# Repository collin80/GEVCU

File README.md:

GEVCU
=====

Generalized Electric Vehicle Control Unit

A project to create a fairly Arduino compatible ECU firmware
to interface with various electric vehicle hardware over canbus
(and possibly other comm channels)

The project builds in the Arduino IDE. So, use it to compile, send the firmware to the Arduino, and monitor serial.
It is suggested though to use the Eclipse based Arduino Plugin by Sloeber which provides far superior capabilities.

The master branch of this project provides a stable code base. The main development happens on the development branch or feature branches if necessary.
If the code on development branch is stable (end tested in practice by the developers), it is merged into the master branch.

You will need the following to have any hope of compiling and running the firmware:
- A GEVCU board. (Versions from 2 upward are supported)
- THe latest Arduino IDE (or preferably Eclipse with ArduinoPlugin by Sloeber)
- due_can library by Collin Kidder
- due_wire library by Collin Kidder
- DueTimer library by Collin Kidder
- PID library by Brett Beauregard

All libraries belong in %USERPROFILE%\Documents\Arduino\libraries (Windows) or ~/Arduino/libraries (Linux/Mac).
You will need to remove -master or any other postfixes. Your library folders should be named as above.

If you use a GEVCU 2.x, please change the pin assignments for CFG_EEPROM_WRITE_PROTECT and CFG_WIFI_RESET in config.h according to comment.      

This software is MIT licensed:

Copyright (c) 2014-2020 Collin Kidder, Michael Neuweiler, Charles Galpin, Jack Rickard

Permission is hereby granted, free of charge, to any person obtaining
a copy of this software and associated documentation files (the
"Software"), to deal in the Software without restriction, including
without limitation the rights to use, copy, modify, merge, publish,
distribute, sublicense, and/or sell copies of the Software, and to
permit persons to whom the Software is furnished to do so, subject to
the following conditions:

The above copyright notice and this permission notice shall be included
in all copies or substantial portions of the Software.

THE SOFTWARE IS PROVIDED "AS IS", WITHOUT WARRANTY OF ANY KIND,
EXPRESS OR IMPLIED, INCLUDING BUT NOT LIMITED TO THE WARRANTIES OF
MERCHANTABILITY, FITNESS FOR A PARTICULAR PURPOSE AND NONINFRINGEMENT.
IN NO EVENT SHALL THE AUTHORS OR COPYRIGHT HOLDERS BE LIABLE FOR ANY
CLAIM, DAMAGES OR OTHER LIABILITY, WHETHER IN AN ACTION OF CONTRACT,
TORT OR OTHERWISE, ARISING FROM, OUT OF OR IN CONNECTION WITH THE
SOFTWARE OR THE USE OR OTHER DEALINGS IN THE SOFTWARE.

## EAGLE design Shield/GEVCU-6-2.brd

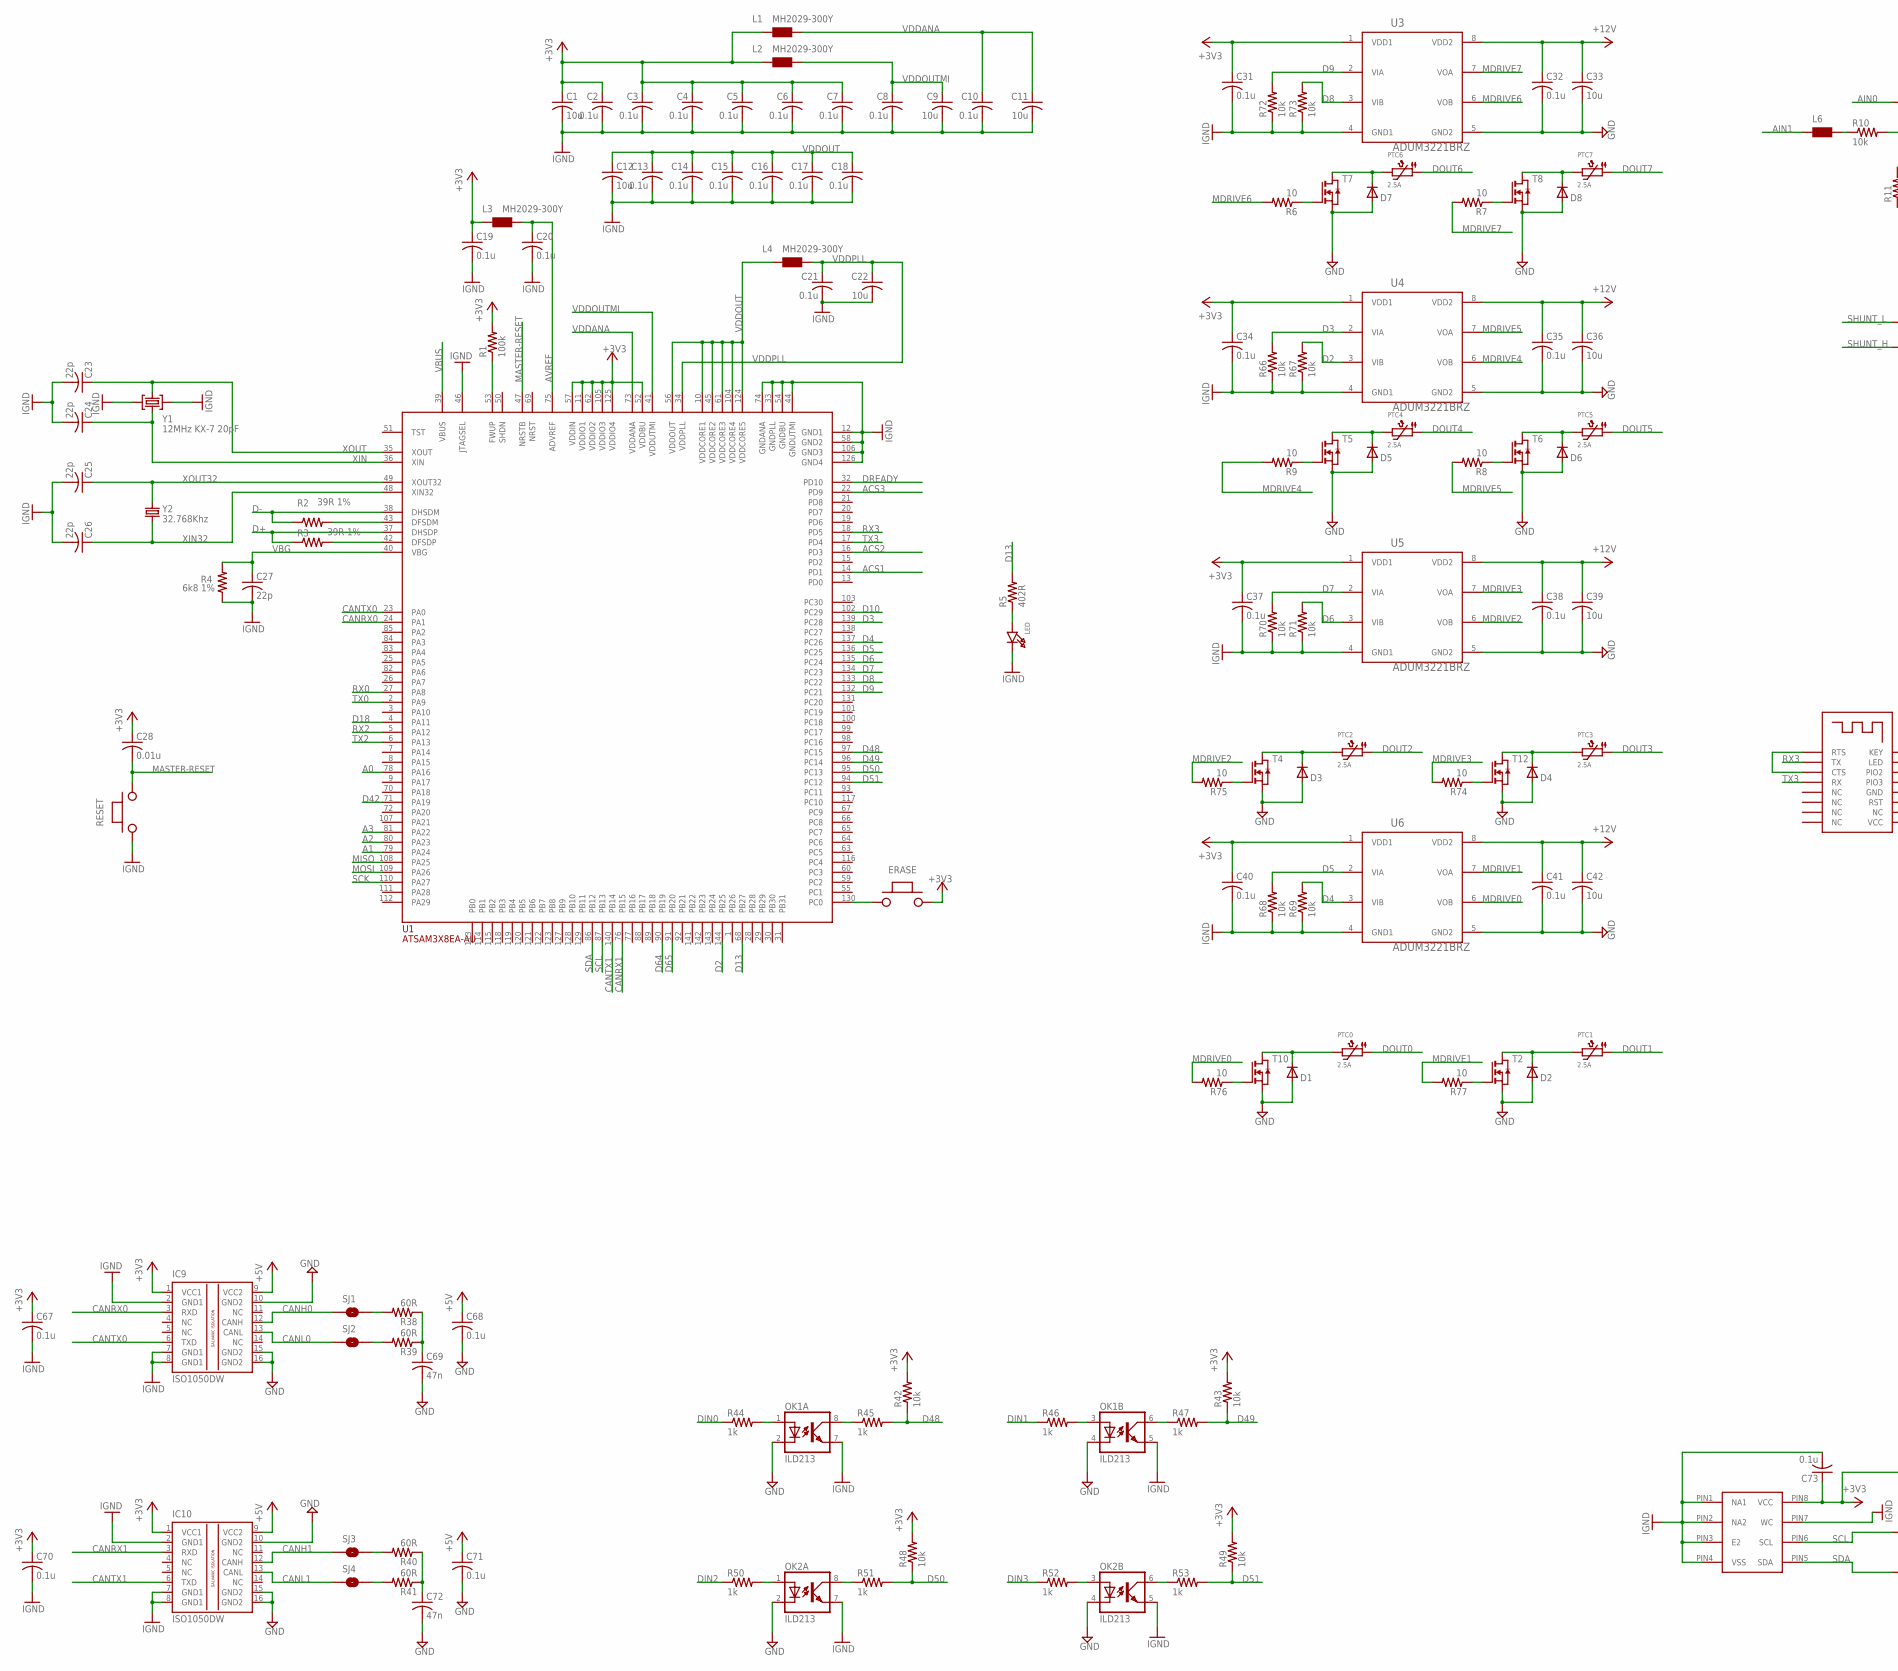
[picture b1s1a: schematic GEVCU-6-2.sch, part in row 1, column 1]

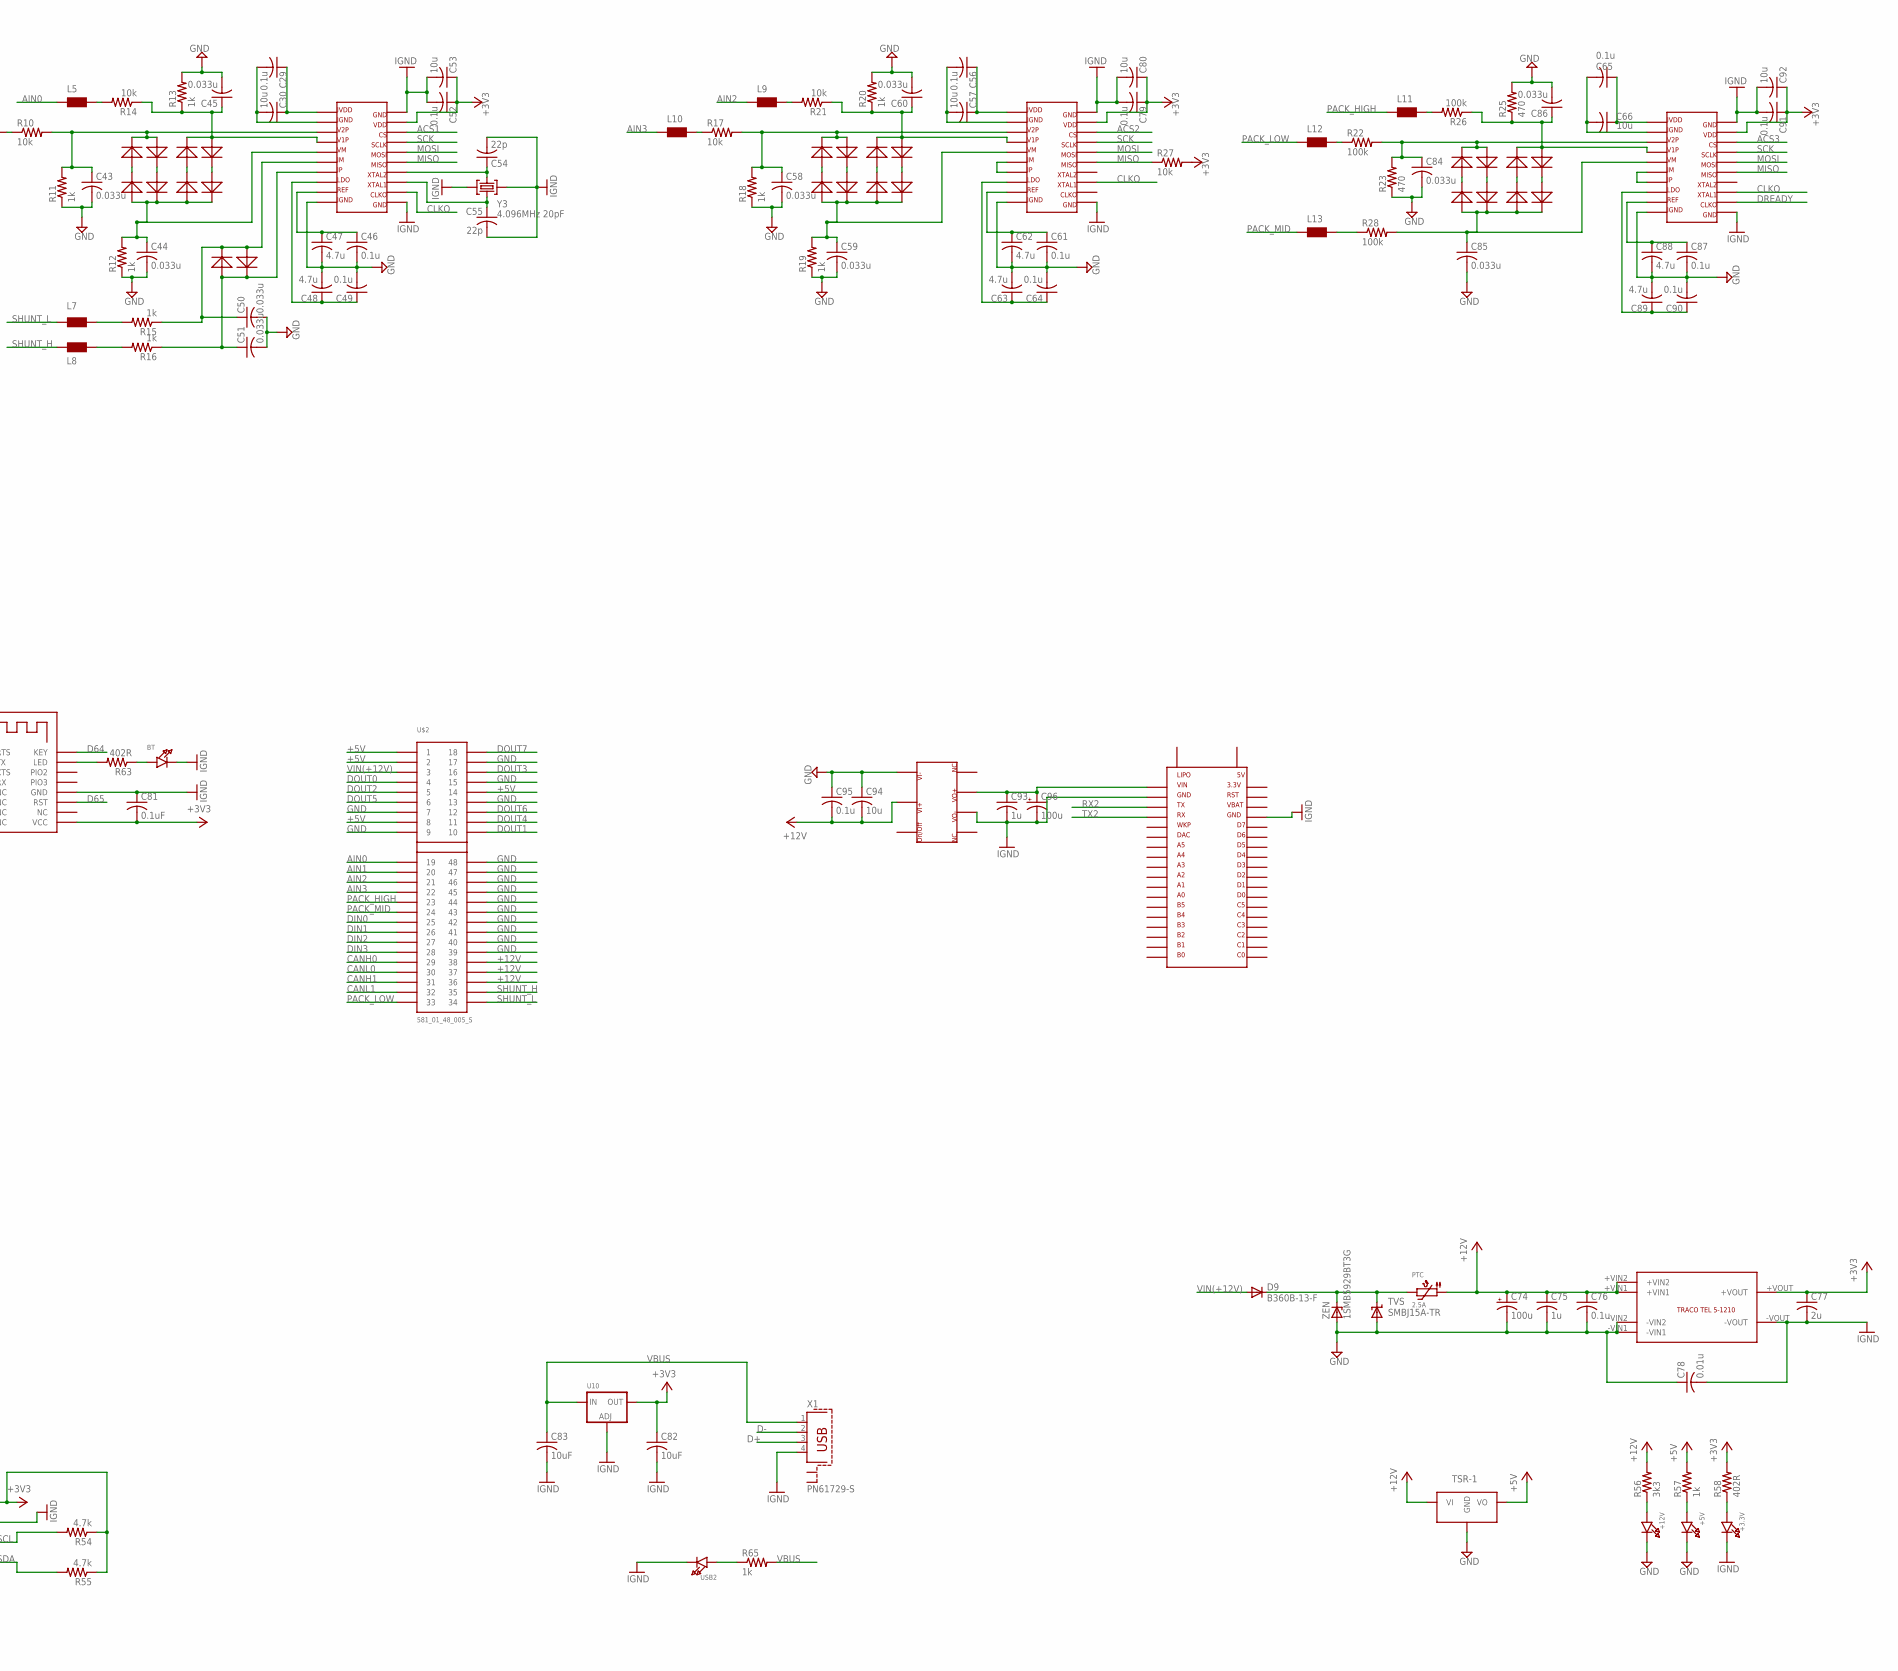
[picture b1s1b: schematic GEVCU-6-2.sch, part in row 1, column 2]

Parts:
+3.3V, +5V, +12V: LED0805; CHIPLED_0805
BT: LED0805; CHIPLED_0805
C1, C9, C11, C12, C22, C30, C33, C36, C39, C42, C53, C57, C66, C80, C92, C94: 10u; C0805
C2, C3, C4, C5, C6, C7, C8, C10, C13, C14, C15, C16, C17, C18, C19, C20, C21, C29, C31, C32, C34, C35, C37, C38, C40, C41, C46, C49, C52, C56, C61, C64, C65, C67, C68, C70, C71, C73, C76, C79, C87, C90, C91, C95: 0.1u; C0805
C23, C24, C54, C55: 22p; C1206
C25, C26, C27: 22p; C0805
C28: 0.01u; C0805
C43, C44, C45, C50, C51, C58, C59, C60, C84, C85, C86: 0.033u; C0805
C47, C48, C62, C63, C88, C89: 4.7u; C0805
C69, C72: 47n; C0805
C74, C96: 100u; E2,5-6
C75, C93: 1u; C0805
C77: 2u; C0805
C78: 0.01u; C1812
C81: 0.1uF; C0805
C82, C83: 10uF; C0805
D1, D2, D3, D4, D5, D6, D7, D8: MBR0520LT; SOD123
D9: B360B-13-F; SMB
D10, D11, D12, D13, D14, D15, D16, D17, D18, D19, D20, D21, D22, D23, D24, D25, D26, D27, D28, D29, D30, D31, D32, D33, D34, D35: SIGDIODE; R0603
ERASE: PUCHBUTTON
IC9, IC10: ISO1050DW; DUB-R-PDSO-G8
L1, L2, L3, L4, L5, L6, L7, L8, L9, L10, L11, L12, L13: MH2029-300Y; 0805
LED: LED0805; CHIPLED_0805
OK1, OK2: ILD213; SOIC08
PTC, PTC0, PTC1, PTC2, PTC3, PTC4, PTC5, PTC6, PTC7: 2.5A; PTC1812
R1, R22, R26, R28: 100k; R0805
R2, R3: 39R 1%; R0805
R4: 6k8 1%; R0805
R5, R58, R63: 402R; R0805
R6, R7, R8, R9, R74, R75, R76, R77: 10; R0805
R10, R14, R17, R21, R27, R42, R43, R48, R49, R66, R67, R68, R69, R70, R71, R72, R73: 10k; R0805
R11, R12, R13, R15, R16, R18, R19, R20, R44, R45, R46, R47, R50, R51, R52, R53, R57, R65: 1k; R0805
R23, R25: 470; R0805
R38, R39, R40, R41: 60R; R0805
R54, R55: 4.7k; R0805
R56: 3k3; R0805
RESET: PUCHBUTTON
SJ1, SJ2, SJ3, SJ4: SOLDERJUMPERNO; SJ_2S-NO
T2, T4, T5, T6, T7, T8, T10, T12: NMOSSOT223; SOT223
TVS: SMBJ15A-TR; SMBJ
U1: ATSAM3X8EA-AU; LQFP144
U3, U4, U5, U6: ADUM3221BRZ; SOIC127P600X175-8N
U7: CK_CUSTOM_M24M02-DRMN6TP; CK_CUSTOM_SOIC8
U8: TRACO
U9: TSR-1
U10: LM1117SOT223-WAVE; SOT223-W
U11, U12, U24: ADE7913; SOIC20
U13: HM-13
U15: ELECTRON
U$1: CINCON5V
U$2: 581_01_48_005_S
USB2: LED0805; CHIPLED_0805
X1: PN61729-S
Y1: 12MHz KX-7 20pF; CRYSTAL-3.2-2.5
Y2: 32.768Khz; ARDUINO_WIFI_SHIELD_V018_TG_RESONATOR_EPSON_FC_145
Y3: 4.096MHz 20pF; CRYSTAL-3.2-2.5
ZEN: 1SMB5929BT3G; SMB

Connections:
+3V3: C1.1, C2.1, C3.1, C4.1, C5.1, C6.1, C7.1, C19.1, C28.1, C31.1, C34.1, C37.1, C40.1, C52.1, C53.1, C67.1, C70.1, C73.1, C77.1, C79.1, C80.1, C81.2, C82.1, C91.1, C92.1, ERASE.P$2, IC9.1 (VCC1), IC10.1 (VCC1), L1.1, L2.1, L3.1, R1.2, R27.2, R42.2, R43.2, R48.2, R49.2, R54.1, R55.1, R58.2, U1.11 (VDDIO1), U1.52 (VDDBU), U1.57 (VDDIN), U1.62 (VDDIO2), U1.105 (VDDIO3), U1.125 (VDDIO4), U3.1 (VDD1), U4.1 (VDD1), U5.1 (VDD1), U6.1 (VDD1), U7.PIN8 (VCC), U8.+VOUT, U10.2 (OUT), U11.19, U12.19, U13.P$9 (VCC), U24.19
+5V: C68.1, C71.1, IC9.9 (VCC2), IC10.9 (VCC2), R57.2, U9.P$3 (VO), U$2.P$1 (1), U$2.P$2 (2), U$2.P$8 (8), U$2.P$14 (14)
+12V: C32.1, C33.1, C35.1, C36.1, C38.1, C39.1, C41.1, C42.1, C74.+, C75.1, C76.1, C94.2, C95.2, PTC.P$1 (1), R56.2, U3.8 (VDD2), U4.8 (VDD2), U5.8 (VDD2), U6.8 (VDD2), U8.+VIN1, U8.+VIN2, U9.P$1 (VI), U$1.P$2, U$2.P$36 (36), U$2.P$37 (37), U$2.P$38 (38)
A0: U1.78 (PA16)
A1: U1.79 (PA24)
A2: U1.80 (PA23)
A3: U1.81 (PA22)
ACS1: U1.14 (PD1), U11.18
ACS2: U1.16 (PD3), U12.18
ACS3: U1.22 (PD9), U24.18
AIN0: L5.1, U$2.P$19 (19)
AIN1: L6.1, U$2.P$20 (20)
AIN2: L9.1, U$2.P$21 (21)
AIN3: L10.1, U$2.P$22 (22)
AVREF: C20.1, L3.2, U1.75 (ADVREF)
CANH0: IC9.12 (CANH), SJ1.1, U$2.P$29 (29)
CANH1: IC10.12 (CANH), SJ3.1, U$2.P$31 (31)
CANL0: IC9.13 (CANL), SJ2.1, U$2.P$30 (30)
CANL1: IC10.13 (CANL), SJ4.1, U$2.P$32 (32)
CANRX0: IC9.3 (RXD), U1.24 (PA1)
CANRX1: IC10.3 (RXD), U1.76 (PB15)
CANTX0: IC9.6 (TXD), U1.23 (PA0)
CANTX1: IC10.6 (TXD), U1.140 (PB14)
CLKO: U11.12, U12.13, U24.13
D2: R67.2, U1.144 (PB25), U4.3 (VIB)
D3: R66.2, U1.139 (PC28), U4.2 (VIA)
D4: R69.2, U1.137 (PC26), U6.3 (VIB)
D5: R68.2, U1.136 (PC25), U6.2 (VIA)
D6: R71.2, U1.135 (PC24), U5.3 (VIB)
D7: R70.2, U1.134 (PC23), U5.2 (VIA)
D8: R73.2, U1.133 (PC22), U3.3 (VIB)
D9: R72.2, U1.132 (PC21), U3.2 (VIA)
D10: U1.102 (PC29)
D13: R5.2, U1.68 (PB27)
D18: U1.4 (PA11)
D42: U1.71 (PA19)
D48: R42.1, R45.2, U1.97 (PC15)
D49: R43.1, R47.2, U1.96 (PC14)
D50: R48.1, R51.2, U1.95 (PC13)
D51: R49.1, R53.2, U1.94 (PC12)
D64: U1.90 (PB19), U13.P$16 (KEY)
D65: U1.91 (PB20), U13.P$11 (RST)
D+: R3.1, U1.37 (DHSDP), X1.3
D-: R2.1, U1.38 (DHSDM), X1.2
DIN0: R44.1, U$2.P$25 (25)
DIN1: R46.1, U$2.P$26 (26)
DIN2: R50.1, U$2.P$27 (27)
DIN3: R52.1, U$2.P$28 (28)
DOUT0: PTC0.P$1 (1), U$2.P$4 (4)
DOUT1: PTC1.P$1 (1), U$2.P$10 (10)
DOUT2: PTC2.P$1 (1), U$2.P$5 (5)
DOUT3: PTC3.P$1 (1), U$2.P$16 (16)
DOUT4: PTC4.P$1 (1), U$2.P$11 (11)
DOUT5: PTC5.P$1 (1), U$2.P$6 (6)
DOUT6: PTC6.P$1 (1), U$2.P$12 (12)
DOUT7: PTC7.P$1 (1), U$2.P$18 (18)
DREADY: U1.32 (PD10), U24.12
ERASE_S: ERASE.P$1, U1.130 (PC0)
GND: +5V.C, +12V.C, C32.2, C33.2, C35.2, C36.2, C38.2, C39.2, C41.2, C42.2, C43.2, C44.2, C45.2, C46.2, C47.2, C48.2, C49.2, C50.2, C51.2, C58.2, C59.2, C60.2, C61.2, C62.2, C63.2, C64.2, C68.2, C69.2, C71.2, C72.2, C74.-, C75.2, C76.2, C78.1, C84.2, C85.2, C86.2, C87.2, C88.2, C89.2, C90.2, C94.1, C95.1, D1.A, D2.A, D3.A, D4.A, D5.A, D6.A, D7.A, D8.A, IC9.10 (GND2), IC9.15 (GND2), IC9.16 (GND2), IC10.10 (GND2), IC10.15 (GND2), IC10.16 (GND2), OK1.2 (C), OK1.4 (C), OK2.2 (C), OK2.4 (C), R11.1, R12.1, R13.2, R18.1, R19.1, R20.2, R23.1, R25.2, T2.3 (S), T4.3 (S), T5.3 (S), T6.3 (S), T7.3 (S), T8.3 (S), T10.3 (S), T12.3 (S), TVS.A, U3.5 (GND2), U4.5 (GND2), U5.5 (GND2), U6.5 (GND2), U8.-VIN1, U8.-VIN2, U9.P$2 (GND), U11.10, U12.10, U24.10, U$1.P$1, U$2.P$7 (7), U$2.P$9 (9), U$2.P$13 (13), U$2.P$15 (15), U$2.P$17 (17), U$2.P$39 (39), U$2.P$40 (40), U$2.P$41 (41), U$2.P$42 (42), U$2.P$43 (43), U$2.P$44 (44), U$2.P$45 (45), U$2.P$46 (46), U$2.P$47 (47), U$2.P$48 (48), ZEN.A
IGND: +3.3V.C, BT.C, C1.2, C2.2, C3.2, C4.2, C5.2, C6.2, C7.2, C8.2, C9.2, C10.2, C11.2, C12.2, C13.2, C14.2, C15.2, C16.2, C17.2, C18.2, C19.2, C20.2, C21.2, C22.2, C23.2, C24.2, C25.2, C26.2, C27.2, C31.2, C34.2, C37.2, C40.2, C52.2, C53.2, C54.2, C55.2, C67.2, C70.2, C73.2, C77.2, C78.2, C79.2, C80.2, C81.1, C82.2, C83.2, C91.2, C92.2, C93.2, C96.-, IC9.2 (GND1), IC9.7 (GND1), IC9.8 (GND1), IC10.2 (GND1), IC10.7 (GND1), IC10.8 (GND1), LED.C, OK1.5 (EMIT), OK1.7 (EMIT), OK2.5 (EMIT), OK2.7 (EMIT), R4.1, R66.1, R67.1, R68.1, R69.1, R70.1, R71.1, R72.1, R73.1, RESET.P$1, U1.12 (GND1), U1.33 (GNDPLL), U1.44 (GNDUTMI), U1.46 (JTAGSEL), U1.54 (GNDBU), U1.58 (GND2), U1.74 (GNDANA), U1.106 (GND3), U1.126 (GND4), U3.4 (GND1), U4.4 (GND1), U5.4 (GND1), U6.4 (GND1), U7.PIN1 (NA1), U7.PIN2 (NA2), U7.PIN3 (E2), U7.PIN4 (VSS), U7.PIN7 (WC), U8.-VOUT, U10.1 (ADJ), U11.11, U11.20, U12.11, U12.20, U13.P$12 (GND), U15.P$17, U15.P$33, U24.11, U24.20, U$1.P$6, USB2.C, X1.4, Y1.2 (GND), Y1.4 (GND), Y3.2 (GND), Y3.4 (GND)
MASTER-RESET: C28.2, RESET.P$2, U1.47 (NRSTB)
MDRIVE0: R76.2, U6.6 (VOB)
MDRIVE1: R77.2, U6.7 (VOA)
MDRIVE2: R75.2, U5.6 (VOB)
MDRIVE3: R74.2, U5.7 (VOA)
MDRIVE4: R9.2, U4.6 (VOB)
MDRIVE5: R8.2, U4.7 (VOA)
MDRIVE6: R6.2, U3.6 (VOB)
MDRIVE7: R7.2, U3.7 (VOA)
MISO: R27.1, U1.108 (PA25), U11.15, U12.15, U24.15
MOSI: U1.109 (PA26), U11.16, U12.16, U24.16
unnamed: D12.2, D13.1
unnamed: +3.3V.A, R58.1
unnamed: D9.C, PTC.P$2 (2), TVS.C, ZEN.C
unnamed: +5V.A, R57.1
unnamed: C29.1, C30.1, U11.1
unnamed: LED.A, R5.1
unnamed: U13.P$1 (RTS), U13.P$3 (CTS)
unnamed: D10.2, D11.1
unnamed: C45.1, D14.2, D16.1, R13.1, R14.1, U11.4
unnamed: C29.2, C30.2, U11.2
unnamed: C43.1, D11.2, D12.1, R10.2, R11.2, U11.3
unnamed: L5.2, R14.2
unnamed: C44.1, D10.1, D13.2, D15.1, D17.2, R12.2, U11.5
unnamed: C65.1, C66.1, U24.1
unnamed: C46.1, C47.1, U11.9
unnamed: C48.1, C49.1, U11.8
unnamed: L6.2, R10.1
unnamed: D16.2, D17.1
unnamed: D14.1, D15.2
unnamed: C50.1, D18.2, D19.1, R15.1, U11.6
unnamed: C51.1, D18.1, D19.2, R16.1, U11.7
unnamed: L7.1, R15.2
unnamed: C56.1, C57.1, U12.1
unnamed: C69.1, R38.1, R39.1
unnamed: L8.1, R16.2
unnamed: R38.2, SJ1.2
unnamed: R39.2, SJ2.2
unnamed: R41.2, SJ4.2
unnamed: C72.1, R40.1, R41.1
unnamed: R40.2, SJ3.2
unnamed: OK1.1 (A), R44.2
unnamed: OK1.3 (A), R46.2
unnamed: OK1.8 (COL), R45.1
unnamed: OK1.6 (COL), R47.1
unnamed: C56.2, C57.2, U12.2
unnamed: OK2.6 (COL), R53.1
unnamed: D22.2, D23.1
unnamed: OK2.8 (COL), R51.1
unnamed: C65.2, C66.2, U24.2
unnamed: OK2.1 (A), R50.2
unnamed: C54.1, U11.14, Y3.3 (C2)
unnamed: C55.1, U11.13, Y3.1 (C1)
unnamed: OK2.3 (A), R52.2
unnamed: +12V.A, R56.1
unnamed: D20.1, D21.2
unnamed: BT.A, R63.1
unnamed: R63.2, U13.P$15 (LED)
unnamed: D2.C, PTC1.P$2 (2), T2.2 (D), T2.4 (D)
unnamed: C58.1, D20.2, D22.1, R17.2, R18.2, U12.3
unnamed: D26.2, D27.1
unnamed: D3.C, PTC2.P$2 (2), T4.2 (D), T4.4 (D)
unnamed: D24.1, D25.2
unnamed: R2.2, U1.43 (DFSDM)
unnamed: C59.1, D21.1, D23.2, D25.1, D27.2, R19.2, U12.5
unnamed: C60.1, D24.2, D26.1, R20.1, R21.1, U12.4
unnamed: R3.2, U1.42 (DFSDP)
unnamed: D5.C, PTC4.P$2 (2), T5.2 (D), T5.4 (D)
unnamed: D6.C, PTC5.P$2 (2), T6.2 (D), T6.4 (D)
unnamed: R1.1, U1.53 (FWUP)
unnamed: D7.C, PTC6.P$2 (2), T7.2 (D), T7.4 (D)
unnamed: D8.C, PTC7.P$2 (2), T8.2 (D), T8.4 (D)
unnamed: D4.C, PTC3.P$2 (2), T12.2 (D), T12.4 (D)
unnamed: D1.C, PTC0.P$2 (2), T10.2 (D), T10.4 (D)
unnamed: D30.2, D31.1
unnamed: C61.1, C62.1, U12.9
unnamed: R65.1, USB2.A
unnamed: R6.1, T7.1 (G)
unnamed: R76.1, T10.1 (G)
unnamed: R77.1, T2.1 (G)
unnamed: R74.1, T12.1 (G)
unnamed: R75.1, T4.1 (G)
unnamed: R9.1, T5.1 (G)
unnamed: R8.1, T6.1 (G)
unnamed: R7.1, T8.1 (G)
unnamed: C63.1, C64.1, U12.8
unnamed: L9.2, R21.2
unnamed: L10.2, R17.1
unnamed: U12.6, U12.7
unnamed: D28.1, D29.2
unnamed: C84.1, D28.2, D30.1, R22.2, R23.2, U24.3
unnamed: D34.2, D35.1
unnamed: D32.1, D33.2
unnamed: C85.1, D29.1, D31.2, D33.1, D35.2, R28.2, U24.5
unnamed: C86.1, D32.2, D34.1, R25.1, R26.1, U24.4
unnamed: C87.1, C88.1, U24.9
unnamed: C89.1, C90.1, U24.8
unnamed: L11.2, R26.2
unnamed: L12.2, R22.1
unnamed: U24.6, U24.7
unnamed: C93.1, C96.+, U15.P$18, U$1.P$5
unnamed: L13.2, R28.1
PACK_HIGH: L11.1, U$2.P$23 (23)
PACK_LOW: L12.1, U$2.P$33 (33)
PACK_MID: L13.1, U$2.P$24 (24)
RX0: U1.27 (PA8)
RX2: U1.5 (PA12), U15.P$16
RX3: U1.18 (PD5), U13.P$2 (TX)
SCK: U1.110 (PA27), U11.17, U12.17, U24.17
SCL: R54.2, U1.87 (PB13), U7.PIN6 (SCL)
SDA: R55.2, U1.86 (PB12), U7.PIN5 (SDA)
SHUNT_H: L8.2, U$2.P$35 (35)
SHUNT_L: L7.2, U$2.P$34 (34)
TX0: U1.2 (PA9)
TX2: U1.6 (PA13), U15.P$15
TX3: U1.17 (PD4), U13.P$4 (RX)
VBG: C27.1, R4.2, U1.40 (VBG)
VBUS: C83.1, R65.2, U1.39 (VBUS), U10.3 (IN), X1.1
VDDANA: C10.1, C11.1, L1.2, U1.73 (VDDANA)
VDDOUT: C12.1, C13.1, C14.1, C15.1, C16.1, C17.1, C18.1, L4.1, U1.10 (VDDCORE1), U1.45 (VDDCORE2), U1.56 (VDDOUT), U1.61 (VDDCORE3), U1.104 (VDDCORE4), U1.124 (VDDCORE5)
VDDOUTMI: C8.1, C9.1, L2.2, U1.41 (VDDUTMI)
VDDPLL: C21.1, C22.1, L4.2, U1.34 (VDDPLL)
VIN(+12V): D9.A, U$2.P$3 (3)
XIN: C24.1, U1.36 (XIN), Y1.1 (C1)
XIN32: C26.1, U1.48 (XIN32), Y2.P$2 (2)
XOUT: C23.1, U1.35 (XOUT), Y1.3 (C2)
XOUT32: C25.1, U1.49 (XOUT32), Y2.P$1 (1)

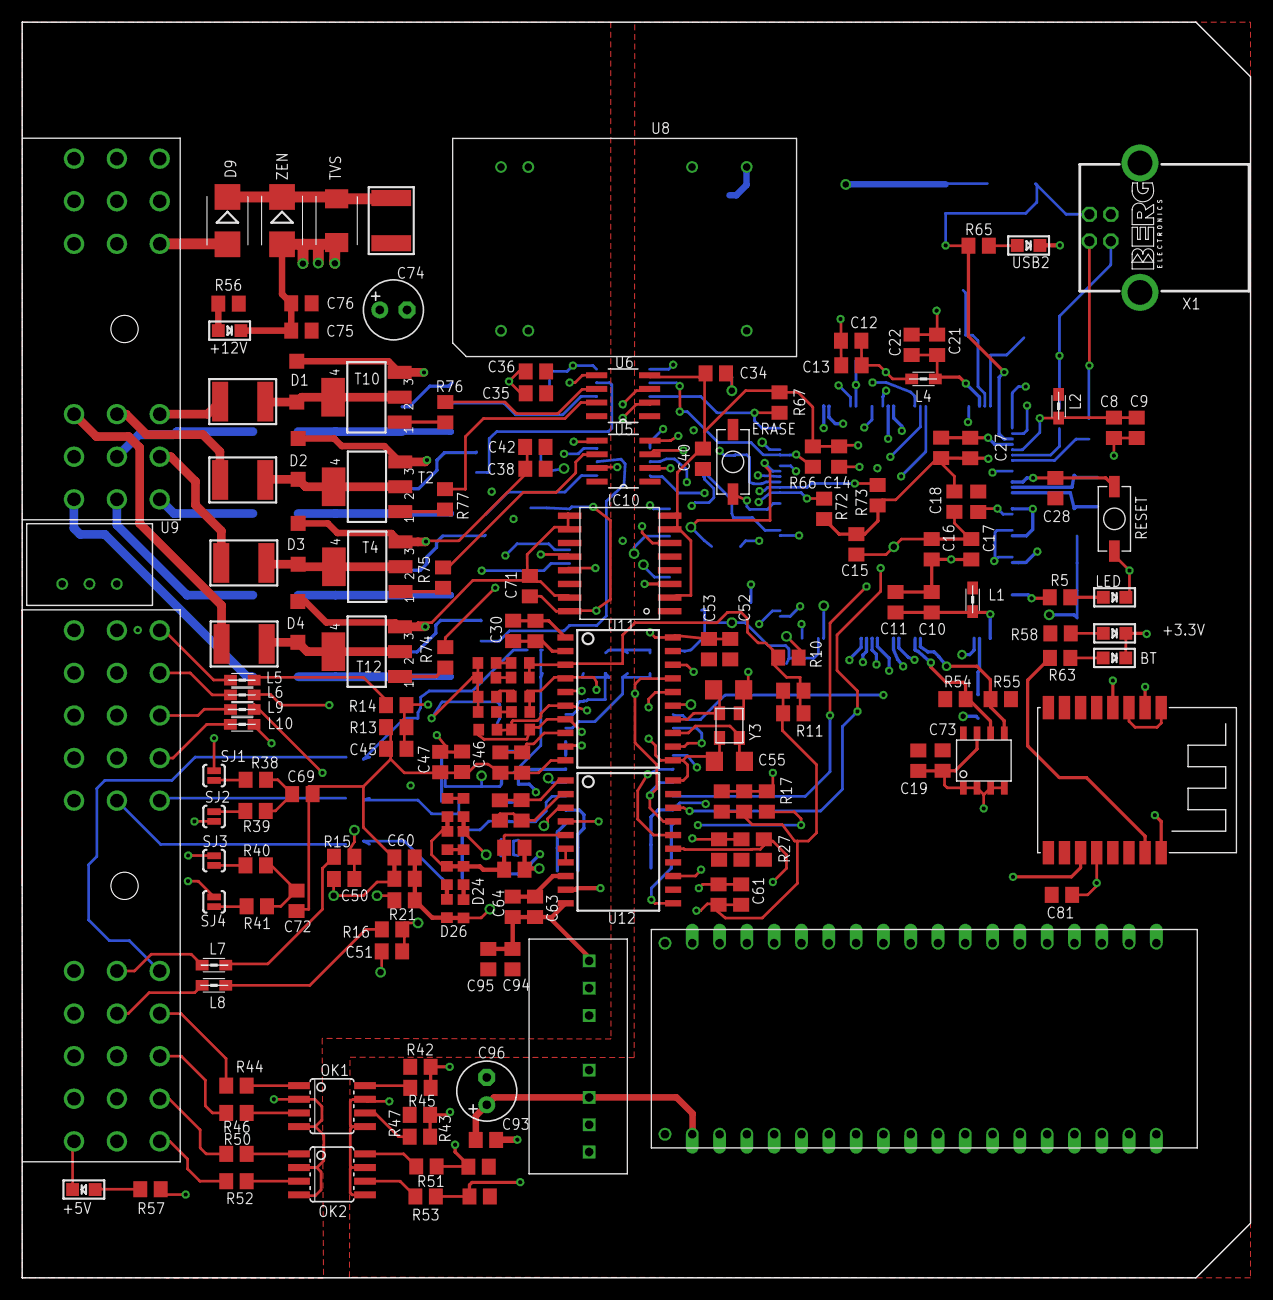
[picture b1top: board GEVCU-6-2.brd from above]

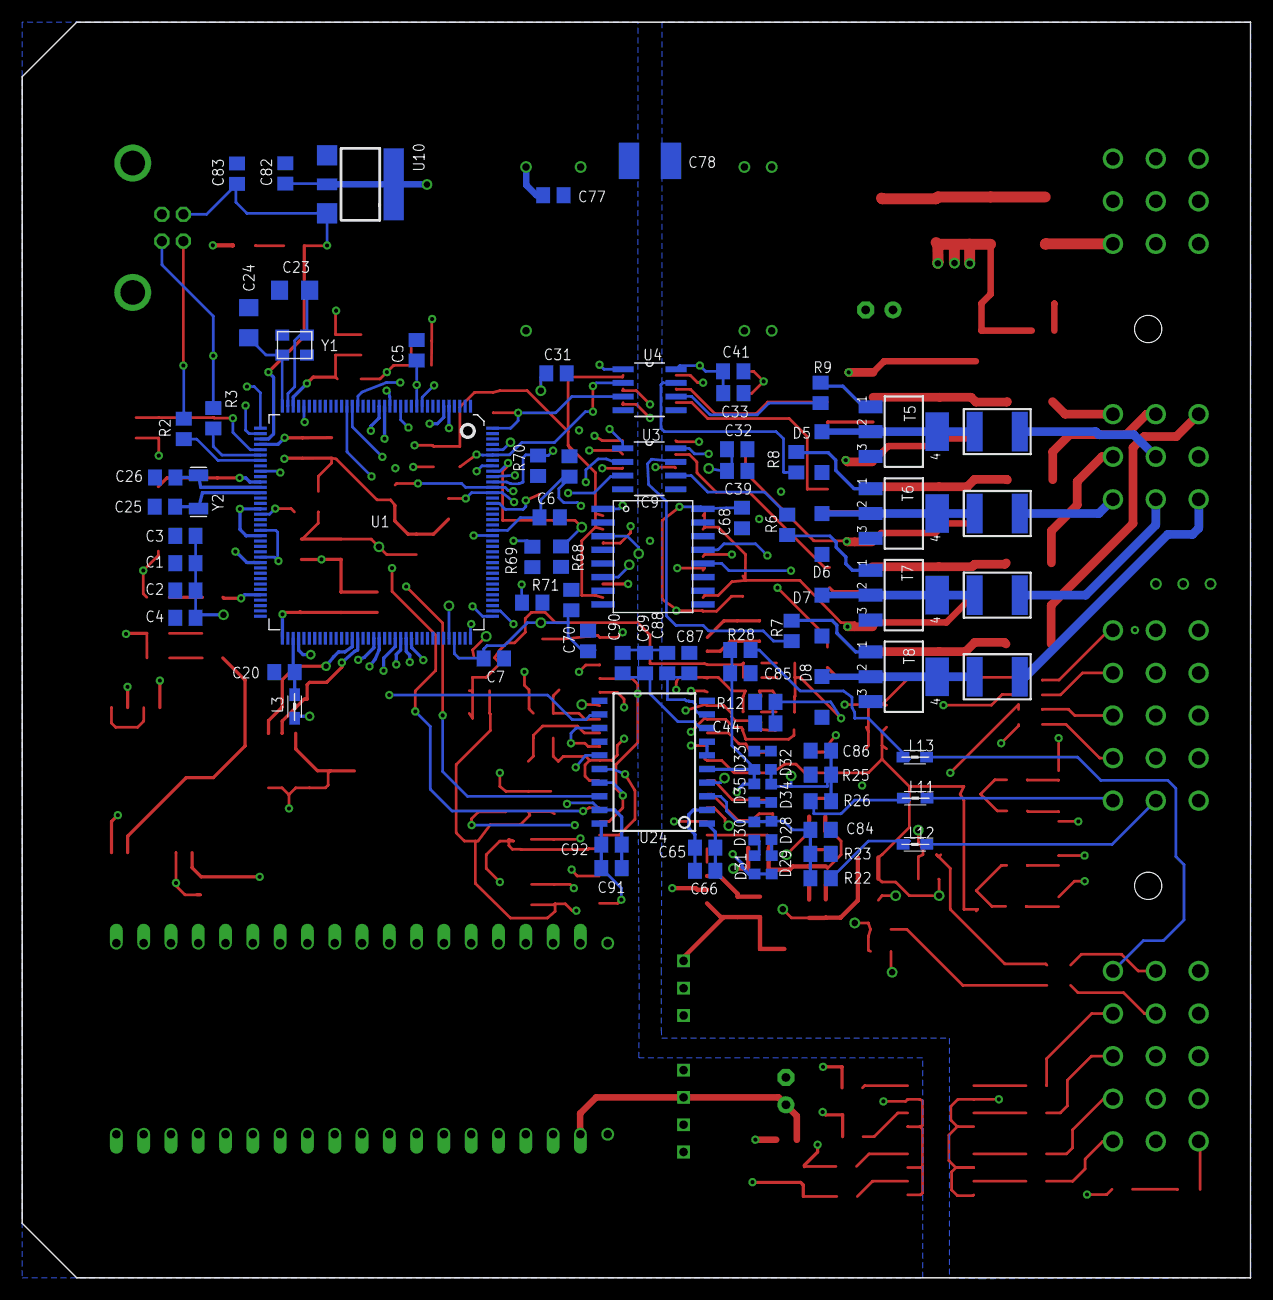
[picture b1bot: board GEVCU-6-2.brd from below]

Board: 4 copper layers, 114.3 x 116.8 mm, 261 parts (85 on the bottom side), 178 nets.

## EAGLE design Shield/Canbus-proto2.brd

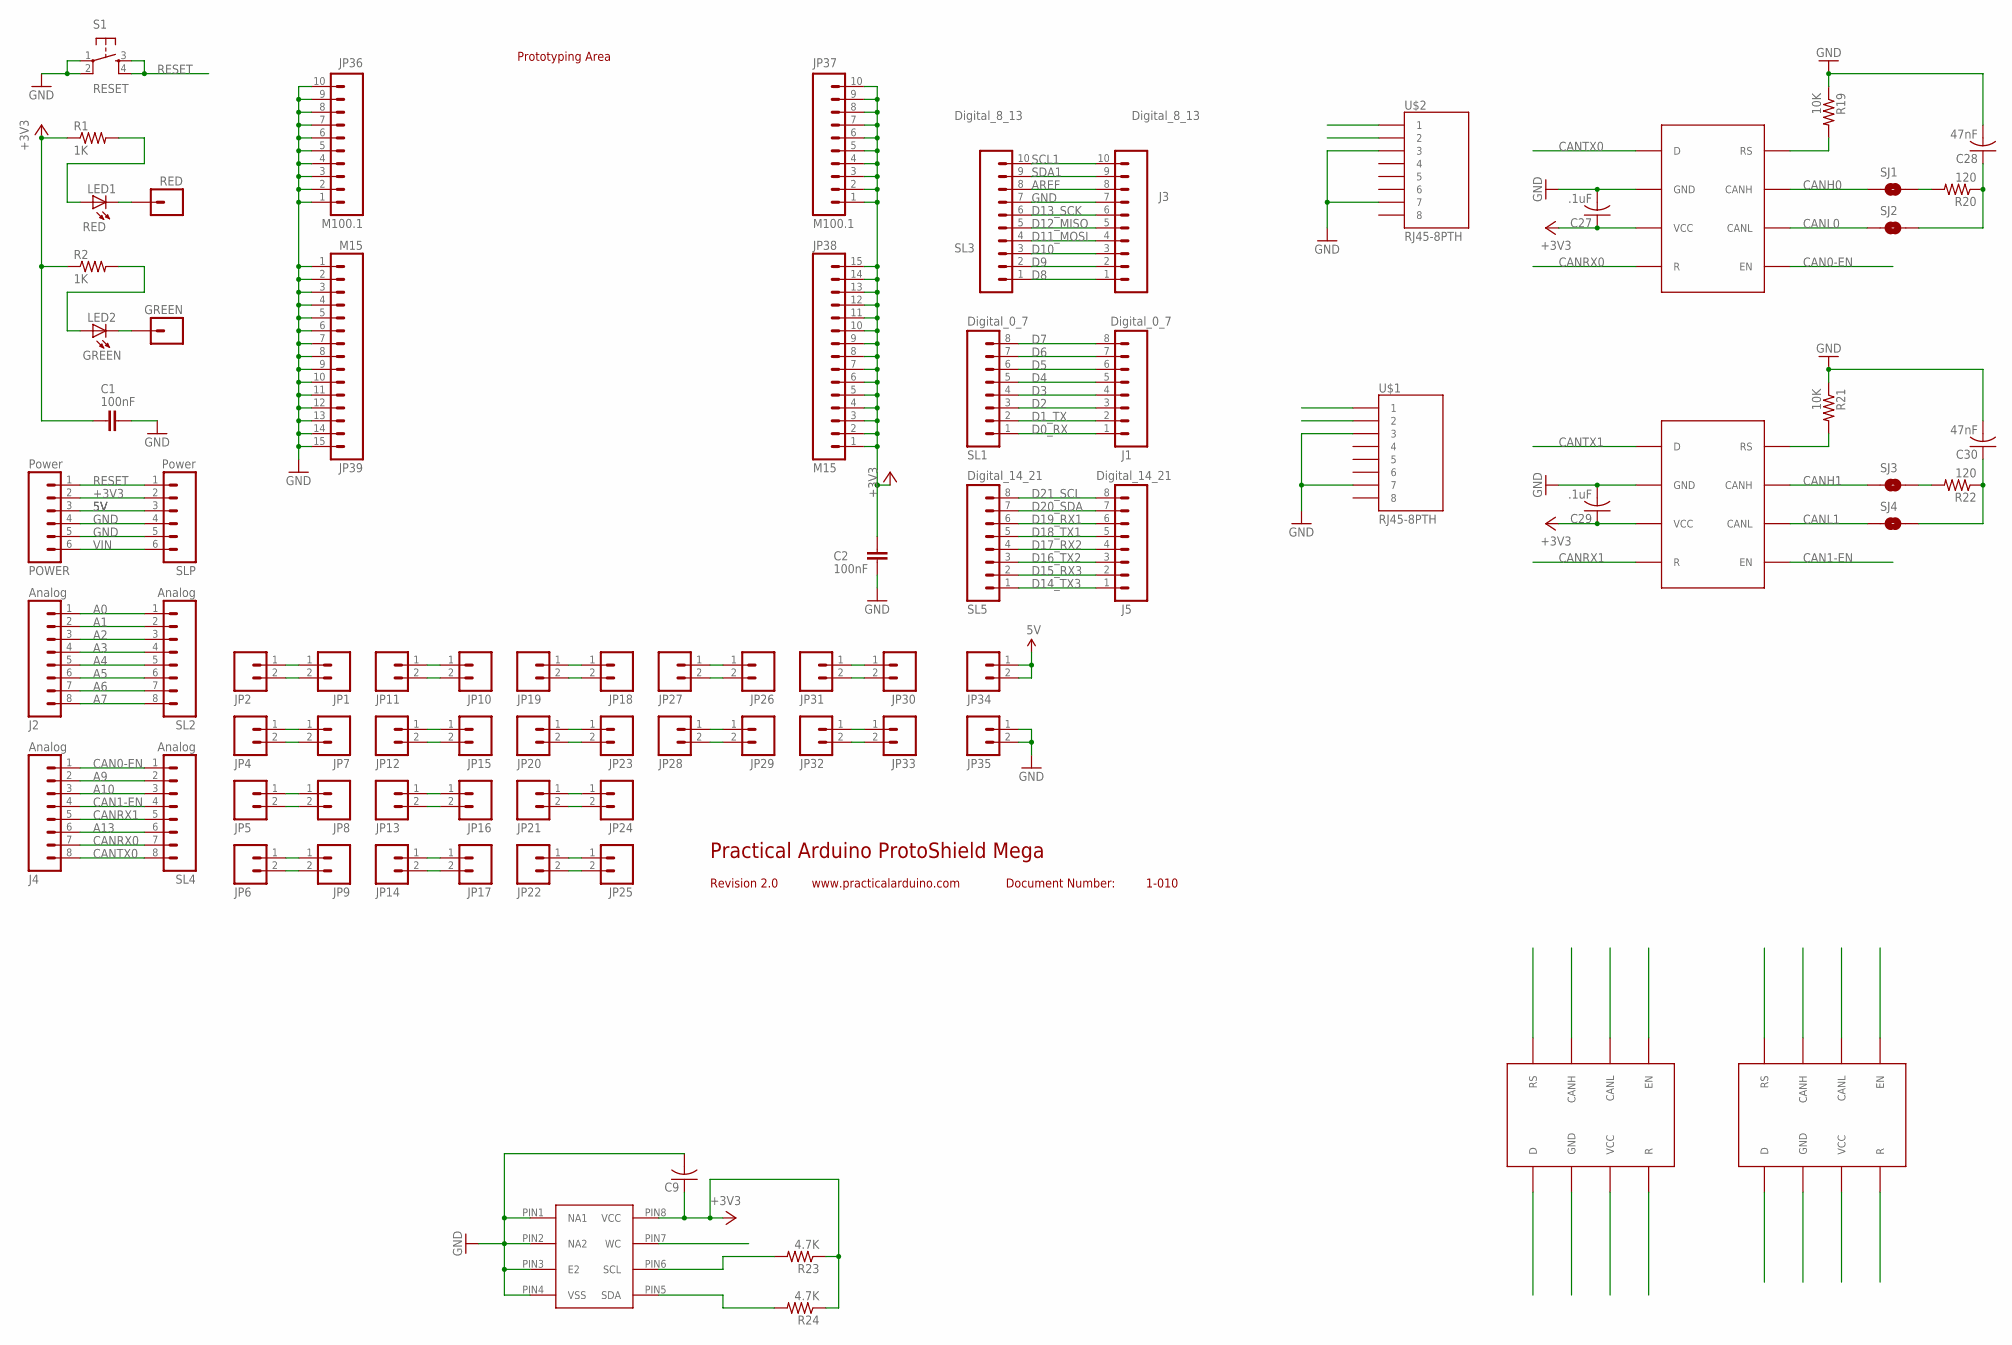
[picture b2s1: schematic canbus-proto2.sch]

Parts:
C1, C2: 100nF; 0603-CAP
C9: C-USC0603; C0603
C27, C29: .1uF; C0603
C28, C30: 47nF; C0603
GREEN: M01PTH; 1X01
J1: Digital_0_7; 1X08
J2, J4: Analog; 1X08
J3: Digital_8_13; 1X10
J5: Digital_14_21; 1X08
JP1, JP2, JP4, JP5, JP6, JP7, JP8, JP9, JP10, JP11, JP12, JP13, JP14, JP15, JP16, JP17, JP18, JP19, JP20, JP21, JP22, JP23, JP24, JP25, JP26, JP27, JP28, JP29, JP30, JP31, JP32, JP33, JP34, JP35: M02PTH; 1X02
JP36, JP37: M100.1; 1X10@1
JP38, JP39: M15; 1X15
LED1: RED; LED-0603
LED2: GREEN; LED-0603
POWER: Power; 1X06
R1, R2: 1K; R0603
R19, R21: 10K; R0603
R20, R22: 120; R0603
R23, R24: 4.7K; R0603
RED: M01PTH; 1X01
S1: RESET; TACTILE-PTH
SJ1, SJ2, SJ3, SJ4: SOLDERJUMPERNO; SJ_2S-NO
SL1: Digital_0_7; 1X08
SL2, SL4: Analog; 1X08
SL3: Digital_8_13; 1X10
SL5: Digital_14_21; 1X08
SLP: Power; 1X06
U$1, U$2: RJ45-8PTH; RJ45-8
U$3, U$4, U$7, U$8: SN65HVD234; SOIC8
U$6: M24M02-DRMN6TP; SOIC8

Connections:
5V: JP34.1, JP34.2, POWER.3, SLP.3
+3V3: C1.1, C2.1, C9.1, C27.1, C29.1, JP37.1, JP37.2, JP37.3, JP37.4, JP37.5, JP37.6, JP37.7, JP37.8, JP37.9, JP37.10, JP38.1, JP38.2, JP38.3, JP38.4, JP38.5, JP38.6, JP38.7, JP38.8, JP38.9, JP38.10, JP38.11, JP38.12, JP38.13, JP38.14, JP38.15, POWER.2, R1.1, R2.1, R23.1, R24.1, SLP.2, U$6.PIN8 (VCC), U$7.PIN3 (VCC), U$8.PIN3 (VCC)
A0: J2.1, SL2.1
A1: J2.2, SL2.2
A2: J2.3, SL2.3
A3: J2.4, SL2.4
A4: J2.5, SL2.5
A5: J2.6, SL2.6
A6: J2.7, SL2.7
A7: J2.8, SL2.8
A9: J4.2, SL4.2
A10: J4.3, SL4.3
A13: J4.6, SL4.6
AREF: J3.8, SL3.8
B1: U$3.PIN8 (RS)
B2: U$3.PIN7 (CANH)
B3: U$3.PIN6 (CANL)
B4: U$3.PIN5 (EN)
B5: U$3.PIN1 (D)
B6: U$3.PIN2 (GND)
B7: U$3.PIN3 (VCC)
B8: U$3.PIN4 (R)
B9: U$4.PIN8 (RS)
B10: U$4.PIN7 (CANH)
B11: U$4.PIN6 (CANL)
B12: U$4.PIN5 (EN)
B13: U$4.PIN4 (R)
B14: U$4.PIN3 (VCC)
B15: U$4.PIN2 (GND)
B16: U$4.PIN1 (D)
CAN0-EN: J4.1, SL4.1, U$7.PIN5 (EN)
CAN1-EN: J4.4, SL4.4, U$8.PIN5 (EN)
CANH0: SJ1.1, U$2.1, U$7.PIN7 (CANH)
CANH1: SJ3.1, U$1.1, U$8.PIN7 (CANH)
CANL0: SJ2.1, U$2.2, U$7.PIN6 (CANL)
CANL1: SJ4.1, U$1.2, U$8.PIN6 (CANL)
CANRX0: J4.7, SL4.7, U$7.PIN4 (R)
CANRX1: J4.5, SL4.5, U$8.PIN4 (R)
CANTX0: J4.8, SL4.8, U$7.PIN1 (D)
CANTX1: JP32.2, JP33.2, U$8.PIN1 (D)
D0_RX: J1.1, SL1.1
D1: JP10.2, JP11.2
D1_TX: J1.2, SL1.2
D2: J1.3, SL1.3
D3: J1.4, SL1.4
D4: J1.5, SL1.5
D5: J1.6, SL1.6
D6: J1.7, SL1.7
D7: J1.8, SL1.8
D8: J3.1, SL3.1
D9: J3.2, SL3.2
D10: J3.3, SL3.3
D11: JP10.1, JP11.1
D11_MOSI: J3.4, SL3.4
D12: JP18.2, JP19.2
D12_MISO: J3.5, SL3.5
D13: JP18.1, JP19.1
D13_SCK: J3.6, SL3.6
D14: JP26.2, JP27.2
D14_TX3: J5.1, SL5.1
D15: JP26.1, JP27.1
D15_RX3: J5.2, SL5.2
D16: JP30.2, JP31.2
D16_TX2: J5.3, SL5.3
D17: JP30.1, JP31.1
D17_RX2: J5.4, SL5.4
D18_TX1: J5.5, SL5.5, U$6.PIN7 (WC)
D19_RX1: J5.6, SL5.6
D20_SDA: J5.7, R24.2, SL5.7, U$6.PIN5 (SDA)
D21_SCL: J5.8, R23.2, SL5.8, U$6.PIN6 (SCL)
D22: JP1.2, JP2.2
D23: JP1.1, JP2.1
GND: C1.2, C2.2, C9.2, C27.2, C28.2, C29.2, C30.2, J3.7, JP35.1, JP35.2, JP36.1, JP36.2, JP36.3, JP36.4, JP36.5, JP36.6, JP36.7, JP36.8, JP36.9, JP36.10, JP39.1, JP39.2, JP39.3, JP39.4, JP39.5, JP39.6, JP39.7, JP39.8, JP39.9, JP39.10, JP39.11, JP39.12, JP39.13, JP39.14, JP39.15, POWER.4, POWER.5, R19.1, R21.1, S1.1, S1.2, SL3.7, SLP.4, SLP.5, U$1.3, U$1.7, U$2.3, U$2.7, U$6.PIN1 (NA1), U$6.PIN2 (NA2), U$6.PIN3 (E2), U$6.PIN4 (VSS), U$7.PIN2 (GND), U$8.PIN2 (GND)
unnamed: LED1.A, R1.2
unnamed: LED1.C, RED.1
unnamed: LED2.A, R2.2
unnamed: GREEN.1, LED2.C
unnamed: R19.2, U$7.PIN8 (RS)
unnamed: JP4.1, JP7.1
unnamed: JP4.2, JP7.2
unnamed: JP5.1, JP8.1
unnamed: JP5.2, JP8.2
unnamed: JP6.1, JP9.1
unnamed: JP6.2, JP9.2
unnamed: JP12.1, JP15.1
unnamed: JP12.2, JP15.2
unnamed: JP13.1, JP16.1
unnamed: JP13.2, JP16.2
unnamed: JP14.1, JP17.1
unnamed: JP14.2, JP17.2
unnamed: JP20.1, JP23.1
unnamed: JP20.2, JP23.2
unnamed: JP21.1, JP24.1
unnamed: JP21.2, JP24.2
unnamed: JP22.1, JP25.1
unnamed: JP22.2, JP25.2
unnamed: JP28.1, JP29.1
unnamed: JP28.2, JP29.2
unnamed: JP32.1, JP33.1
unnamed: C28.1, R20.1, SJ2.2
unnamed: R20.2, SJ1.2
unnamed: R21.2, U$8.PIN8 (RS)
unnamed: C30.1, R22.1, SJ4.2
unnamed: R22.2, SJ3.2
RESET: POWER.1, S1.3, S1.4, SLP.1
SCL1: J3.10, SL3.10
SDA1: J3.9, SL3.9
VIN: POWER.6, SLP.6

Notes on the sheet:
Prototyping Area
Practical Arduino ProtoShield Mega
Revision 2.0
www.practicalarduino.com
Document Number:
1-010

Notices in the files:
parts and their libraries:
SparkFun-Connectors: Licensing: CC v3.0 Share-Alike You are welcome to use this library for commercial purposes.
microbuilder: This work is placed in the public domain, and may be freely used for commercial and non-commercial work with the following conditions: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
